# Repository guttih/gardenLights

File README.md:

# gardenLights
A project to control my RGB IR controlled 
remote garden lights using esp32 and VoffCon.

## Projects in this repository
### Light Remote
The [Remote controller] Controls a spotlight
### Lights Commander
The [Lights Commander] Commands one or many Light Controllers

### VoffCon
The [VoffCon] A control card and a control used to send commands to the 
Lights Commander

[Remote controller]: ./remoteController/README.md
[Lights Commander]: ./lightsCommander/README.md
[VoffCon]: ./voffCon/README.md

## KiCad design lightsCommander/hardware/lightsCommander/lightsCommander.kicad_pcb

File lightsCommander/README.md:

# gardenLights - lightsCommander
This project will take commands from VoffCon and send them to the 
lightController(s).

This project is one of two applications the researched on this [web page].

# Connections
Description on how to wire the esp32 to the 

| PIN | NRF24L01 | Esp32 Development module |
| --- | -------: | :----------------------- |
| 1   | GND      | GND                      |
| 2   | VCC      | 3V3                      |
| 3   | CE       | D12                      |
| 4   | CSN      | D14                      |
| 5   | SCK      | D18                      |
| 6   | MOSI     | D23                      |
| 7   | MISO     | D19                      |
| 8   | IRQ      | -                        |

[web page]: https://guttih.com/list/project-garden-lights

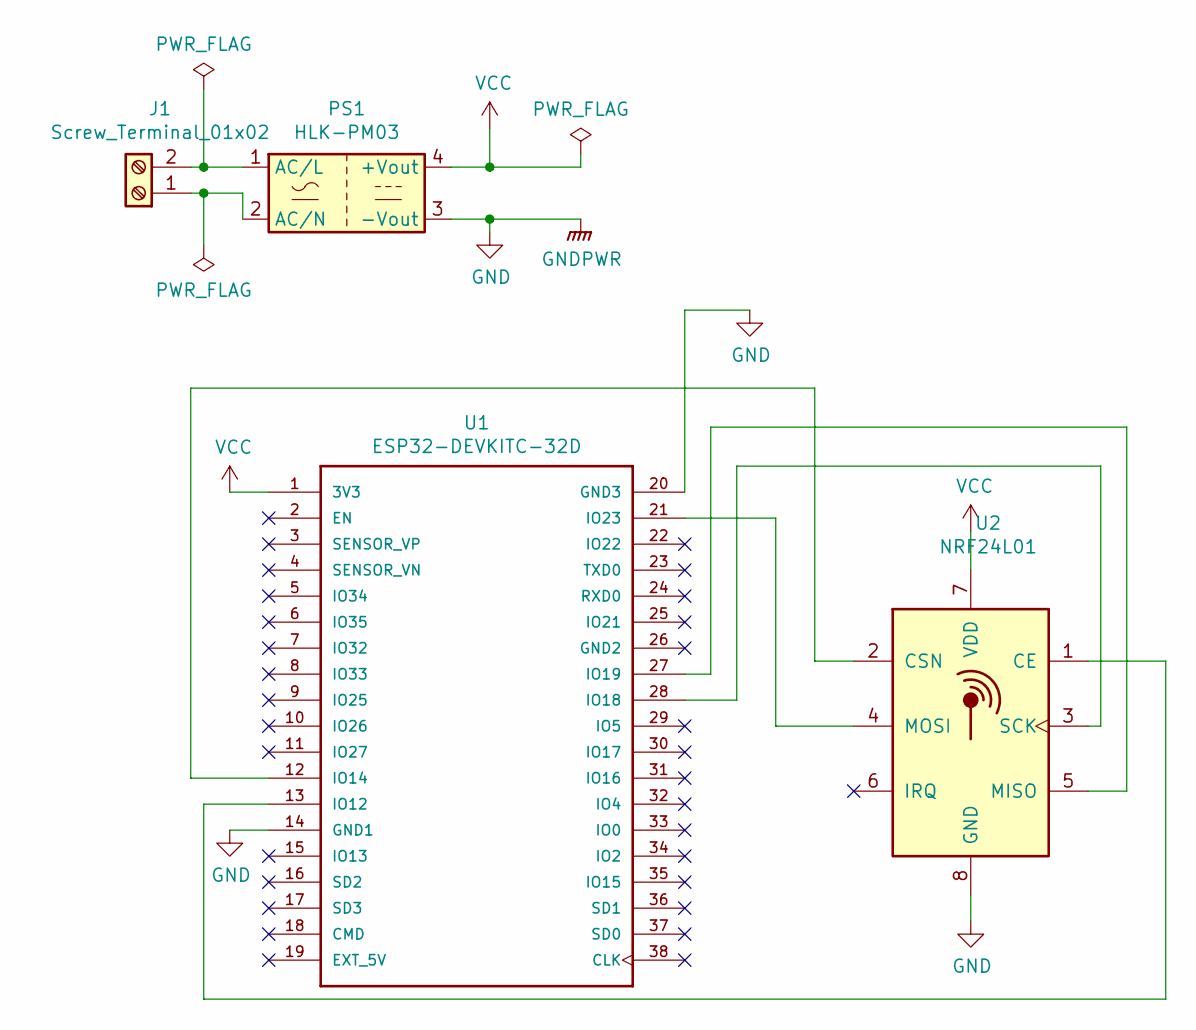
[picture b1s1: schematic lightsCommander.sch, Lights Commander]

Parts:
J1: Screw_Terminal_01x02; Screw_Termianl_01x02
PS1: HLK-PM03; Converter_ACDC_HiLink_HLK-PMxx
U1: ESP32-DEVKITC-32D; ESP32-DevKitC
U2: NRF24L01; nRF24L01_Breakout_longRange

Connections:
GND: PS1.3 (-Vout), U1.14 (GND1), U1.20 (GND3), U2.8 (GND)
unnamed: J1.1, PS1.2 (AC/N)
unnamed: J1.2, PS1.1 (AC/L)
unnamed: U1.12 (IO14), U2.2 (CSN)
unnamed: U1.13 (IO12), U2.1 (CE)
unnamed: U1.21 (IO23), U2.4 (MOSI)
unnamed: U1.27 (IO19), U2.5 (MISO)
unnamed: U1.28 (IO18), U2.3 (SCK)
VCC: PS1.4 (+Vout), U1.1 (3V3), U2.7 (VDD)

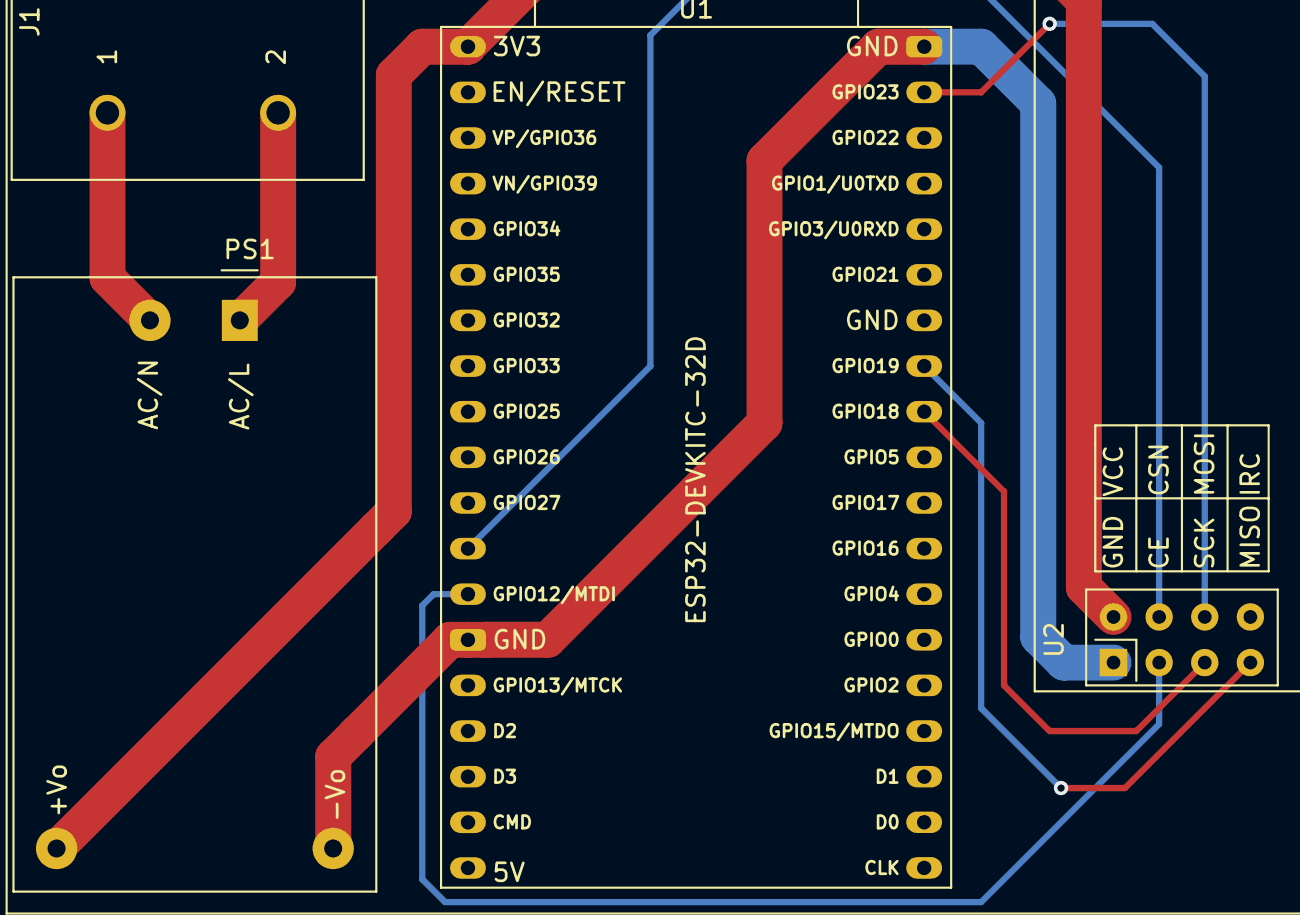
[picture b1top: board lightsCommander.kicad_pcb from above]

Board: 2 copper layers, 4 parts (0 on the bottom side), 9 nets.

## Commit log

2021-09-18 creating folder structure
2021-09-18 fixing readme paths
2021-09-18 renaming voffcon
2021-09-18 renameing voffcon to voffCon
2021-09-18 voffCon with uppercase C
2021-09-19 Both projects are building
2021-09-19 renaming lightController to remoteController
2021-09-19 created a pcb for LightsCommander

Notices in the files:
lightsCommander/hardware/lightsCommander/lightsCommander.kicad_pcb:
Licence: CC BY 4.0
lightsCommander/hardware/lightsCommander/lightsCommander.sch:
https://creativecommons.org/licenses/by/4.0
